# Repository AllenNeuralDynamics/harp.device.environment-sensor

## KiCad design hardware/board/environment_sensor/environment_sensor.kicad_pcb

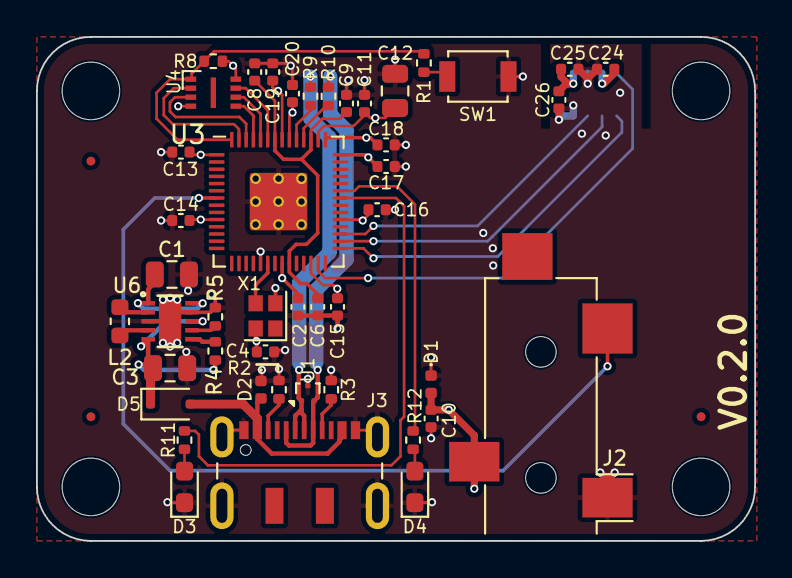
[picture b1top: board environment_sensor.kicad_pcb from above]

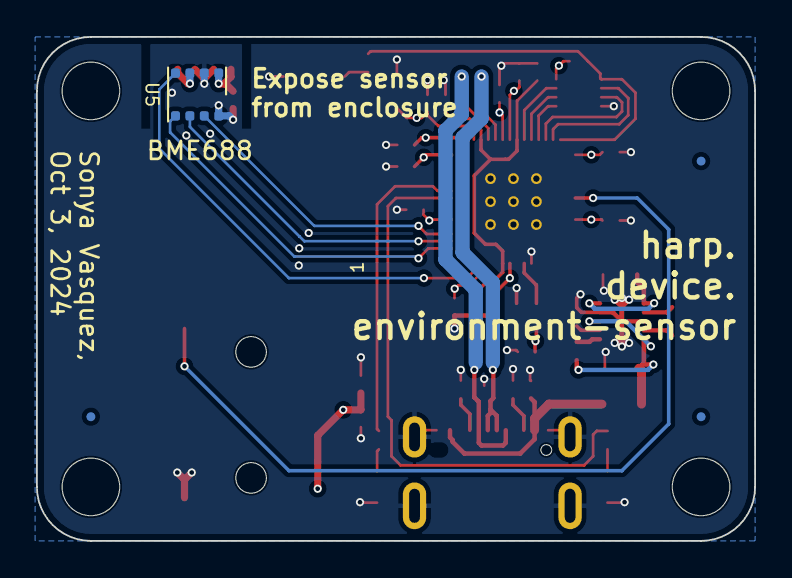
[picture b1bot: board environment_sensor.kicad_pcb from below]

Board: 4 copper layers, 39.9 x 28.0 mm, 52 parts (4 on the bottom side), 32 nets.

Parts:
C1: 22uF; C_0805_2012Metric
C2, C6, C8, C13, C14, C15, C16, C17, C18, C19, C20, C24, C25: 100nF; C_0402_1005Metric
C3, C12: 10uF; C_0805_2012Metric
C4: 10nF; C_0402_1005Metric
C9, C10, C11, C26: 1uF; C_0402_1005Metric
D1, D2: D_TVS; D_0402_1005Metric
D3, D4: LED; LED_0603_1608Metric_Pad1.05x0.95mm_HandSolder
D5: BAT54J; D_SOD-323F
FID1, FID2, FID3, FID4, FID5, FID6: Fiducial; Fiducial_0.5mm_Mask1mm
J2: AudioJack3; Jack_3.5mm_CUI_SJ-3524-SMT_Horizontal
J3: USB_C_Receptacle_USB2.0; USB_C_Receptacle_JAE_DX07S016JA1R1500
L2: 2.2uH; L_0603_1608Metric
R1: 1K; R_0402_1005Metric
R2, R3: 5K1; R_0402_1005Metric
R4, R5: 100K; R_0402_1005Metric
R8: 10K; R_0402_1005Metric
R9, R10: 27; R_0402_1005Metric
R11, R12: 330; R_0402_1005Metric
SW1: SW_Push; SW_SPST_B3U-1000P
U1: TPD2EUSB30; Texas_DRT-3
U3: RP2040; RP2040-QFN-56
U4: W25Q16JVUXIQ; Winbond-8USON-2x3mm
U5: BME688; Bosch_LGA-8_3x3mm_P0.8mm_ClockwisePinNumbering
U6: rt6150b-33gqw; WDFN-10-1EP_2.5x2.5mm_P0.5_EP1.25x2.1mm
X1: ECS-TXO-2016; Crystal_SMD_2016-4Pin_2.0x1.6mm

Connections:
+1V1: C6.2, C8.2, C9.1, U3.23 (DVDD), U3.45 (VREG_VOUT), U3.50 (DVDD)
+3V3: C1.2, C2.2, C4.1, C10.1, C11.1, C12.1, C13.2, C14.2, C15.2, C16.2, C17.2, C18.2, C19.2, C20.2, C24.2, C25.2, C26.1, D1.2 (A2), J2.R, R8.2, U3.1 (IOVDD), U3.10 (IOVDD), U3.22 (IOVDD), U3.26 (RUN), U3.33 (IOVDD), U3.42 (IOVDD), U3.43 (ADC_AVDD), U3.44 (VREG_IN), U3.48 (USB_VDD), U3.49 (IOVDD), U4.8 (VCC), U5.6 (VDDIO), U5.8 (VDD), U6.1 (VOUT), U6.10 (FB), X1.4 (VDD)
/Harp Core RP2040 + USB/CS: U3.31 (GPIO20), U5.2 (CSB)
/Harp Core RP2040 + USB/D+: J3.A6 (D+), J3.B6 (D+), R9.2, U1.1 (D+)
/Harp Core RP2040 + USB/D-: J3.A7 (D-), J3.B7 (D-), R10.2, U1.2 (D-)
/Harp Core RP2040 + USB/HARP_CLK_SYNC: J2.T, U3.7 (GPIO5)
/Harp Core RP2040 + USB/PICO: U3.30 (GPIO19), U5.3 (SDI)
/Harp Core RP2040 + USB/POCI: U3.27 (GPIO16), U5.5 (SDO)
/Harp Core RP2040 + USB/QSPI_CLK: U3.52 (QSPI_SCLK), U4.6 (CLK)
/Harp Core RP2040 + USB/QSPI_CS: R1.2, R8.1, U3.56 (QSPI_SS), U4.1 (~CS)
/Harp Core RP2040 + USB/QSPI_D0: U3.53 (QSPI_SD0), U4.5 (DI(IO0))
/Harp Core RP2040 + USB/QSPI_D1: U3.55 (QSPI_SD1), U4.2 (DO(IO1))
/Harp Core RP2040 + USB/QSPI_D2: U3.54 (QSPI_SD2), U4.3 (IO2)
/Harp Core RP2040 + USB/QSPI_D3: U3.51 (QSPI_SD3), U4.7 (IO3)
/Harp Core RP2040 + USB/SCK: U3.29 (GPIO18), U5.4 (SCK)
/Harp Core RP2040 + USB/USB_Boot: R1.1, SW1.2
GND: C1.1, C2.1, C3.2, C4.2, C6.1, C8.1, C9.2, C10.2, C11.2, C12.2, C13.1, C14.1, C15.1, C16.1, C17.1, C18.1, C19.1, C20.1, C24.1, C25.1, C26.2, D1.1 (A1), D2.1 (A1), D3.1 (K), D4.1 (K), J2.S, J3.A1 (GND), J3.A12 (GND), J3.B1 (GND), J3.B12 (GND), J3.S1 (SHIELD), R2.2, R3.2, R5.2, SW1.1, U1.3 (GND), U3.19 (TESTEN), U3.57 (GND), U4.4 (GND), U5.1 (GND), U5.7 (GND), U6.3 (GND), U6.9 (GND), U6.11 (GND), X1.2 (GND)
unnamed: D3.2 (A), R11.2
unnamed: D4.2 (A), R12.2
unnamed: J3.A5 (CC1), R2.1
unnamed: J3.B5 (CC2), R3.1
unnamed: R11.1, U3.36 (GPIO24)
unnamed: R12.1, U3.37 (GPIO25)
unnamed: R10.1, U3.46 (USB_DM)
unnamed: R9.1, U3.47 (USB_DP)
unnamed: U3.20 (XIN), X1.3 (OUT)
unnamed: R4.1, U6.6 (EN)
unnamed: L2.1, U6.4 (LX1)
unnamed: L2.2, U6.2 (LX2)
unnamed: R5.1, U6.7 (PS)
VBUS: D2.2 (A2), D5.2 (A), J3.A4 (VBUS), J3.A9 (VBUS), J3.B4 (VBUS), J3.B9 (VBUS)
VDD: C3.1, D5.1 (K), R4.2, U6.5 (VIN), U6.8 (VINA)

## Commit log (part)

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2024-10-23 Update WhoAmI
2024-10-23 Add device.yml
2024-10-23 Update harp.core.rp2040 pin
2024-10-29 Clean up unused code
2024-10-29 Add doxygen comments
2024-10-29 Refactor shim functions into Arduino.h
2024-10-29 Put magic numbers in config.h
2024-10-29 Clean up code
2024-10-29 Add proper humidity units (prh)
2024-10-30 Update harp device name
2024-10-30 Put harp device name in config.h
2024-10-31 Read info and whoAmI from device.yml
2024-11-07 Update target schema
2024-11-07 Add register access modifiers
2024-11-07 Add first draft of bonsai interface
2024-11-08 Make de-multiplexed registers read-only
2024-11-08 Expose multiplexed sensor data via nested object
2024-11-08 Simplify interface to enable/disable events
2024-11-08 Regenerate interface
2024-11-08 Make EnableEvents forward compatible with more flags
2024-11-08 update 3d shapes for audio jack
2024-11-08 Update bonsai generators to embedded device metadata in assembly
2024-11-10 Favor harp-tech as source of device schema
2024-11-14 Add python script and cli to read values
2024-11-14 Add note for SIPE computers to point to pypi
2024-11-22 Add --device-yaml arg with default
2024-12-10 Add update_interval_s cli arg to continuous mode
2024-12-10 Update README.md with update_interval_s
2025-01-21 Update README.md with instructions for windows dev
2025-02-06 adding temperature offset and adjustment to lower sys clock speed
2025-02-07 adding function call to configure clock
2025-02-14 Update pyharp commit pin
2025-02-19 update how PICO_SDK_PATH is searched for
2025-02-19 removing call in main to slow down clocks
2025-02-19 change path diagnostic msg
2025-02-19 add events-enabled check
2025-02-19 add offset as register; tweak event dispatch criteria
2025-02-19 remove redefines already in harp core
2025-02-19 bump version
2025-03-06 Ignore local vscode settings
2025-03-06 Regenerate Bonsai interface
2025-03-06 Bump package version and add package type metadata
    Further docs regarding metadata in https://bonsai-rx.org/docs/articles/create-package.html
2025-10-28 making change to rel humidity calculation as per Daniel Alvarez analysis
2025-11-03 remove clock config, and increment version
2025-11-07 adding defines for relative humidty constants
